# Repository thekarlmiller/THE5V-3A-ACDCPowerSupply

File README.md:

# THE5V-3A-ACDCPowerSupply
THEIoTHomeAutomation modulee for adding a 5V power supply to an ESP32 project

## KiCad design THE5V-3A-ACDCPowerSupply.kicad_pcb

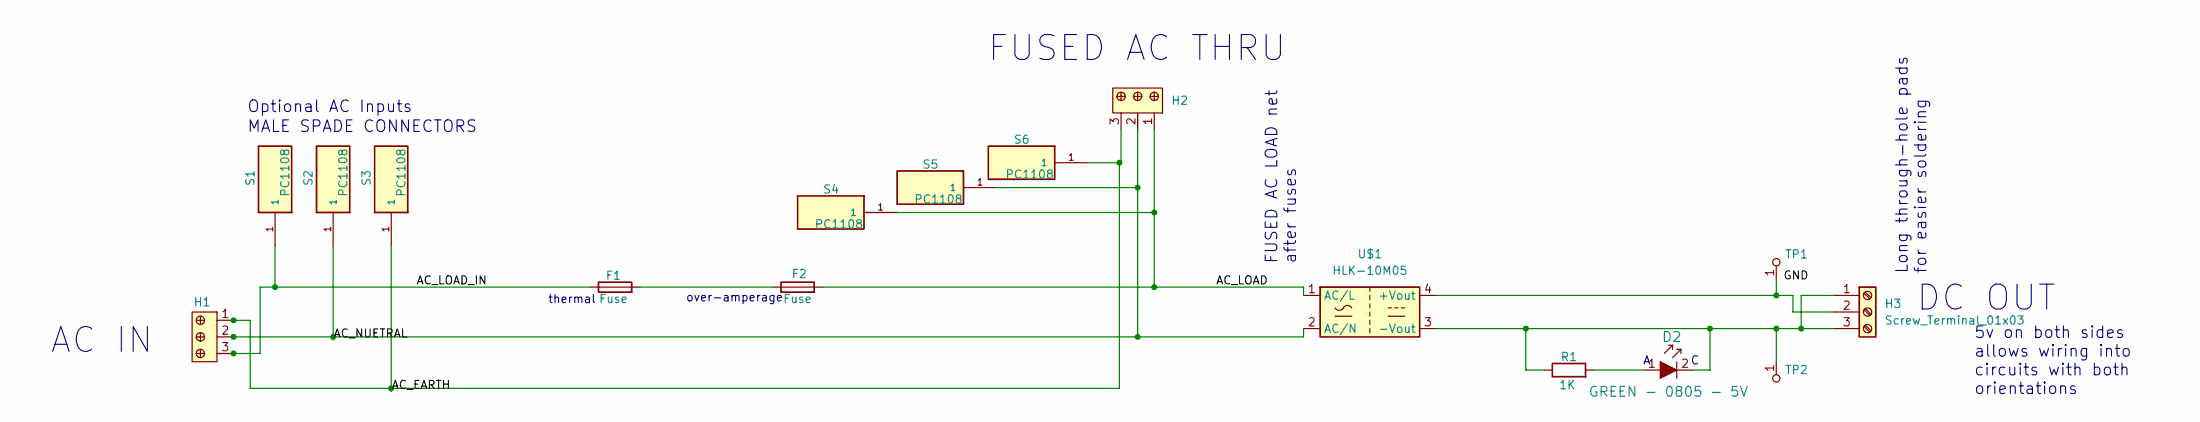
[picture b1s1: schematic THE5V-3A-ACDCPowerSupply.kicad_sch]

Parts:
D2: GREEN - 0805 - 5V; LED_0805_2012Metric; MPN LG R971-KN-1
F1, F2: Fuse; Fuseholder_Keystone_3555-2
H1, H2: OSTTC032162; TERM_BLOCK_1x3_P5.08MM; MPN OSTTC032162
H3: Screw_Terminal_01x03; TERM_BLOCK_1x3_P5.08MM
R1: 1K; R_0805_2012Metric
S1, S2, S3, S4, S5, S6: PC1108; TERMINAL_PC1108; PARTREV A
TP1, TP2: Test-Point-Pin_Drill2.79mm; MPN 1508-0-57-15-00-00-03-0
U$1: HLK-10M05; Converter_ACDC_Hi-Link_HLK-10Mxx

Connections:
/AC_EARTH: H1.1, H2.3, S3.1, S6.1
/AC_LOAD: F2.2, H2.1, S4.1, U$1.1 (AC/L)
/AC_LOAD_IN: F1.1, H1.3, S1.1
/AC_NUETRAL: H1.2, H2.2, S2.1, S5.1, U$1.2 (AC/N)
unnamed: D2.1, R1.2
unnamed: F1.2, F2.1
unnamed: D2.2, H3.1, H3.3, R1.1, TP2.1, U$1.3 (-Vout)
unnamed: H3.2, TP1.1, U$1.4 (+Vout)

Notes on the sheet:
AC IN
5v on both sides allows wiring into circuits with both orientations
over-amperage
Long through-hole pads for easier soldering
thermal
MALE SPADE CONNECTORS
Optional AC Inputs
DC OUT
FUSED AC THRU
FUSED AC LOAD net after fuses

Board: 2 copper layers, 16 parts (2 on the bottom side), 8 nets, no tracks yet.
